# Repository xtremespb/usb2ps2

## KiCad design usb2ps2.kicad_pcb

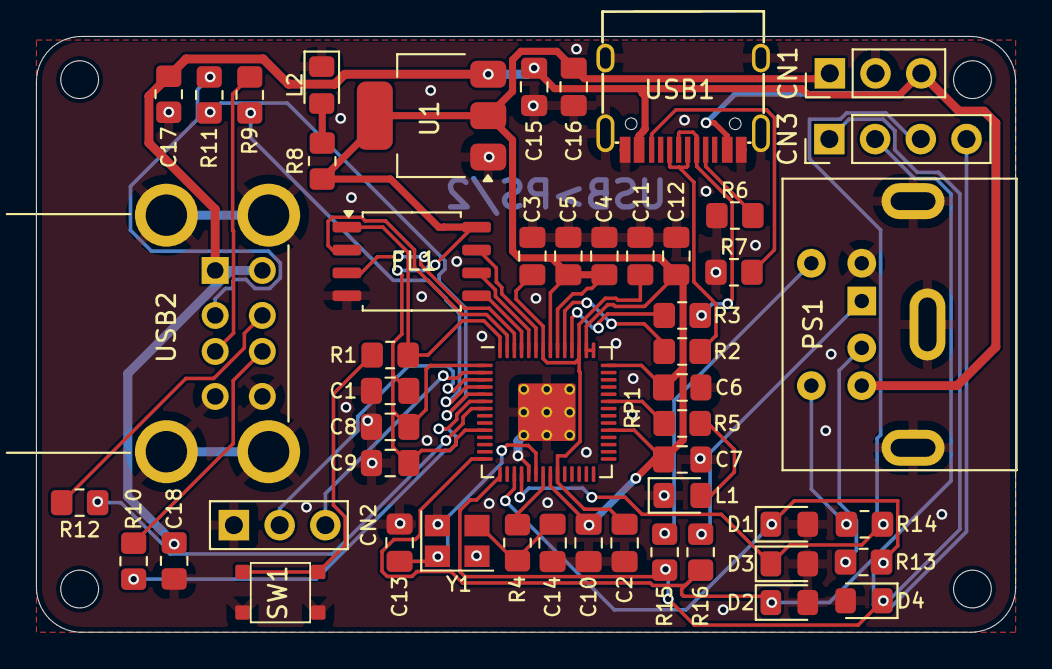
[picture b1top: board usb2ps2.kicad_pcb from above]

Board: 2 copper layers, 54.4 x 33.1 mm, 55 parts (0 on the bottom side), 41 nets.

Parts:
C1, C2, C3, C4, C5, C6, C7, C8, C9, C10: 100n; Medved_C_0805
C11, C12: 1u; Medved_C_0805
C13, C14: 15p; Medved_C_0805
C15, C16: 10u; Medved_C_0805
C17, C18: 10u; Medved_R_0805
CN1: Conn_01x03_Pin; PinHeader_1x03_P2.54mm_Vertical
CN2: UART; Medved_UART_Pin3
CN3: PS/2 Pins; PinHeader_1x04_P2.54mm_Vertical
D1, D2, D3, D4: 3V3; Medved_D_0805
FL1: W25Q128JVS; Medved_SOIC-8_5.23x5.23mm_P1.27mm
H1, H2, H3, H4: MountingHole; MountingHole_2.1mm
L1, L2: LED; Medved_LED_0805
PS1: PS/2; Connector_Mini-DIN_Female_6Pin_2rows
R1, R4: 1k; Medved_R_0805
R2, R3: 27; Medved_R_0805
R5, R8: 1K; Medved_R_0805
R6, R7: 5.1K; Medved_R_0805
R9, R10, R11, R12: 22R; Medved_R_0805
R13, R14, R15, R16: 100R; Medved_R_0805
RP1: RP2040; RP2040-QFN-56
SW1: Flash Button; Button_SMD_3x3x2
U1: NCP1117-3.3_SOT223; Medved_SOT-223-3_TabPin2
USB1: USB Type C; USB-TYPE-C-31-M-12_lib2
USB2: USB_A_Stacked; Medved_USB_A_CUI_UJ2-ADH-TH_Horizontal_Stacked
Y1: ABM8-272-T3; Crystal_SMD_3225-4Pin_3.2x2.5mm

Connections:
+3V3: C1.1, C4.1, C5.1, C6.1, C7.1, C8.1, C9.1, C10.1, C12.1, C16.1, CN1.1, FL1.8 (VCC), R8.2, RP1.1 (IOVDD), RP1.10 (IOVDD), RP1.22 (IOVDD), RP1.33 (IOVDD), RP1.42 (IOVDD), RP1.43 (ADC_AVDD), RP1.44 (VREG_IN), RP1.48 (USB_VDD), RP1.49 (IOVDD), U1.2 (VO)
/D+: R2.1, USB1.6 (DP1), USB1.8 (DP2)
/D-: R3.1, USB1.5 (DN2), USB1.7 (DN1)
/GPIO0: CN2.1, RP1.2 (GPIO0)
/GPIO1: CN2.2, RP1.3 (GPIO1)
/GPIO2: R9.1, RP1.4 (GPIO2)
/GPIO3: R11.1, RP1.5 (GPIO3)
/GPIO4: R10.1, RP1.6 (GPIO4)
/GPIO5: R12.1, RP1.7 (GPIO5)
/GPIO11: CN3.2, D2.1 (K), R16.2, RP1.14 (GPIO11)
/GPIO12: CN3.1, D4.1 (K), R15.2, RP1.15 (GPIO12)
/GPIO14: CN3.4, D1.1 (K), R13.2, RP1.17 (GPIO14)
/GPIO15: CN3.3, D3.1 (K), R14.2, RP1.18 (GPIO15)
/PS2 with Diodes/KB_CLK: PS1.5, R15.1
/PS2 with Diodes/KB_DATA: PS1.1, R16.1
/PS2 with Diodes/MS_CLK: PS1.6, R14.1
/PS2 with Diodes/MS_DATA: PS1.2, R13.1
/RP2040/GPIO25: R5.2, RP1.37 (GPIO25)
/RP2040/QSPI_SCLK: FL1.6 (CLK), RP1.52 (QSPI_SCLK)
/RP2040/QSPI_SD0: FL1.5 (DI(IO0)), RP1.53 (QSPI_SD0)
/RP2040/QSPI_SD1: FL1.2 (DO(IO1)), RP1.55 (QSPI_SD1)
/RP2040/QSPI_SD2: FL1.3 (IO2), RP1.54 (QSPI_SD2)
/RP2040/QSPI_SD3: FL1.7 (IO3), RP1.51 (QSPI_SD3)
/RP2040/QSPI_SS: FL1.1 (~CS), R1.1, RP1.56 (QSPI_SS)
/RP2040/XIN: C13.1, RP1.20 (XIN), Y1.1
/RP2040/XOUT: R4.1, RP1.21 (XOUT)
/RP2040/~USB_BOOT: R1.2, SW1.3, SW1.4
GND: C1.2, C2.2, C3.2, C4.2, C5.2, C6.2, C7.2, C8.2, C9.2, C10.2, C11.2, C12.2, C13.2, C14.2, C15.2, C16.2, C17.2, C18.2, CN1.2, CN2.3, D1.2 (A), D2.2 (A), D3.2 (A), D4.2 (A), FL1.4 (GND), L1.1 (K), L2.1 (K), PS1.3, R6.1, R7.1, RP1.19 (TESTEN), RP1.57 (GND), SW1.1, SW1.2, U1.1 (GND), USB1.1 (GND), USB1.12 (GND), USB1.13 (SHIELD), USB2.4 (GND1), USB2.8 (GND2), USB2.9 (Shield), Y1.2, Y1.4
unnamed: C14.1, R4.2, Y1.3
unnamed: L1.2 (A), R5.1
unnamed: L2.2 (A), R8.1
unnamed: R3.2, RP1.46 (USB_DM)
unnamed: R2.2, RP1.47 (USB_DP)
unnamed: C2.1, C3.1, C11.1, RP1.23 (DVDD), RP1.45 (VREG_VOUT), RP1.50 (DVDD)
unnamed: R6.2, USB1.4 (CC1)
unnamed: R7.2, USB1.10 (CC2)
unnamed: R9.2, USB2.3 (D1+)
unnamed: R11.2, USB2.2 (D1-)
unnamed: R10.2, USB2.7 (D2+)
unnamed: R12.2, USB2.6 (D2-)
VBUS: C15.1, C17.1, C18.1, CN1.3, PS1.4, U1.3 (VI), USB1.2 (VBUS), USB1.11 (VBUS), USB2.1 (VBUS1), USB2.5 (VBUS2)

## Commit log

2024-10-25 Gerbers & Schematics added
2024-10-25 HW Rev 1.0
2024-11-13 HW Rev. 1.1
2024-11-13 Added schematics
2024-11-28 Minor updates
2024-12-06 Case added
2024-12-07 HW Rev 1.2
2024-12-07 Gerbers added
2024-12-08 HW Rev 1.2 minor fixes
